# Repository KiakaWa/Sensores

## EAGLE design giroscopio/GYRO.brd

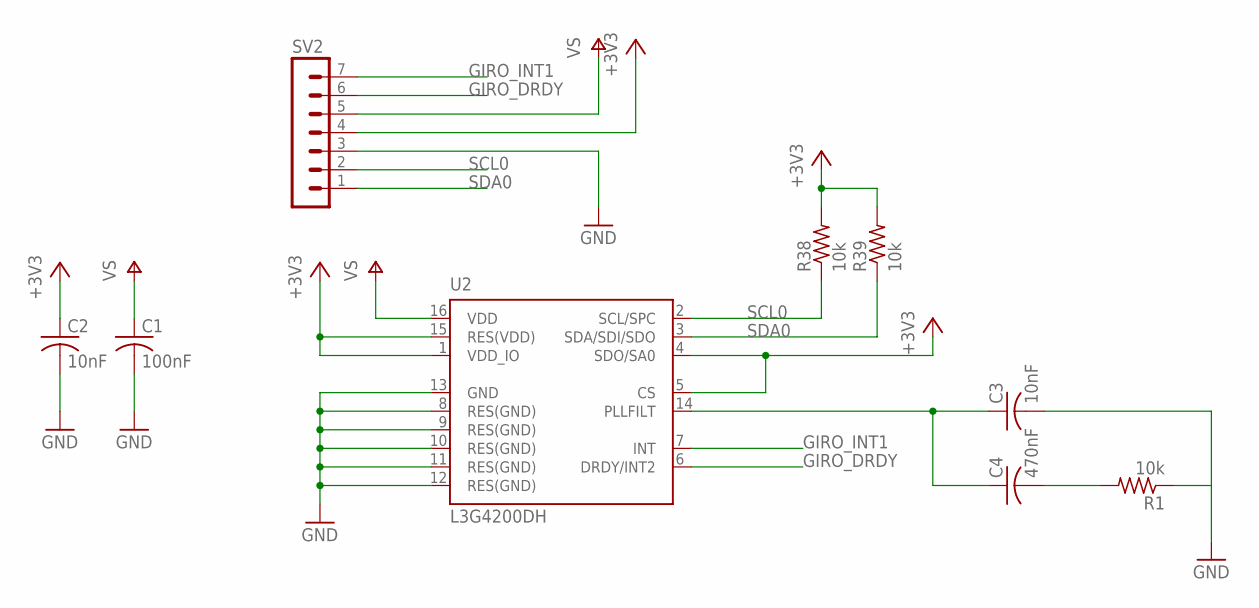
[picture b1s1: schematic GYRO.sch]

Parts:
C1: 100nF; C0805
C2, C3: 10nF; C0805
C4: 470nF; C0805
R1, R38, R39: 10k; R0805
SV2: MA07-1
U2: L3G4200DH; LGA-16L

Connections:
+3V3: C2.1, R38.2, R39.2, SV2.4, U2.1 (VDD_IO), U2.4 (SDO/SA0), U2.5 (CS), U2.15 (RES(VDD))
GIRO_DRDY: SV2.6, U2.6 (DRDY/INT2)
GIRO_INT1: SV2.7, U2.7 (INT)
GND: C1.2, C2.2, C3.2, R1.1, SV2.3, U2.8 (RES(GND)), U2.9 (RES(GND)), U2.10 (RES(GND)), U2.11 (RES(GND)), U2.12 (RES(GND)), U2.13 (GND)
unnamed: C3.1, C4.1, U2.14 (PLLFILT)
unnamed: C4.2, R1.2
SCL0: R38.1, SV2.2, U2.2 (SCL/SPC)
SDA0: R39.1, SV2.1, U2.3 (SDA/SDI/SDO)
V+: C1.1, SV2.5, U2.16 (VDD)

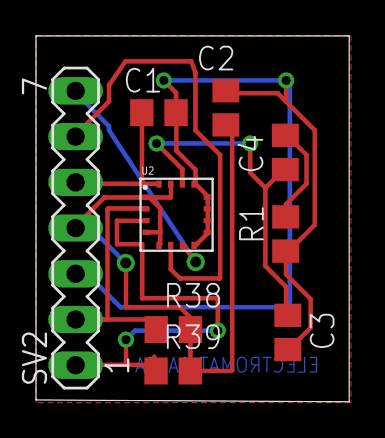
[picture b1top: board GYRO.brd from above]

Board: 2 copper layers, 17.4 x 20.3 mm, 9 parts (0 on the bottom side), 9 nets.

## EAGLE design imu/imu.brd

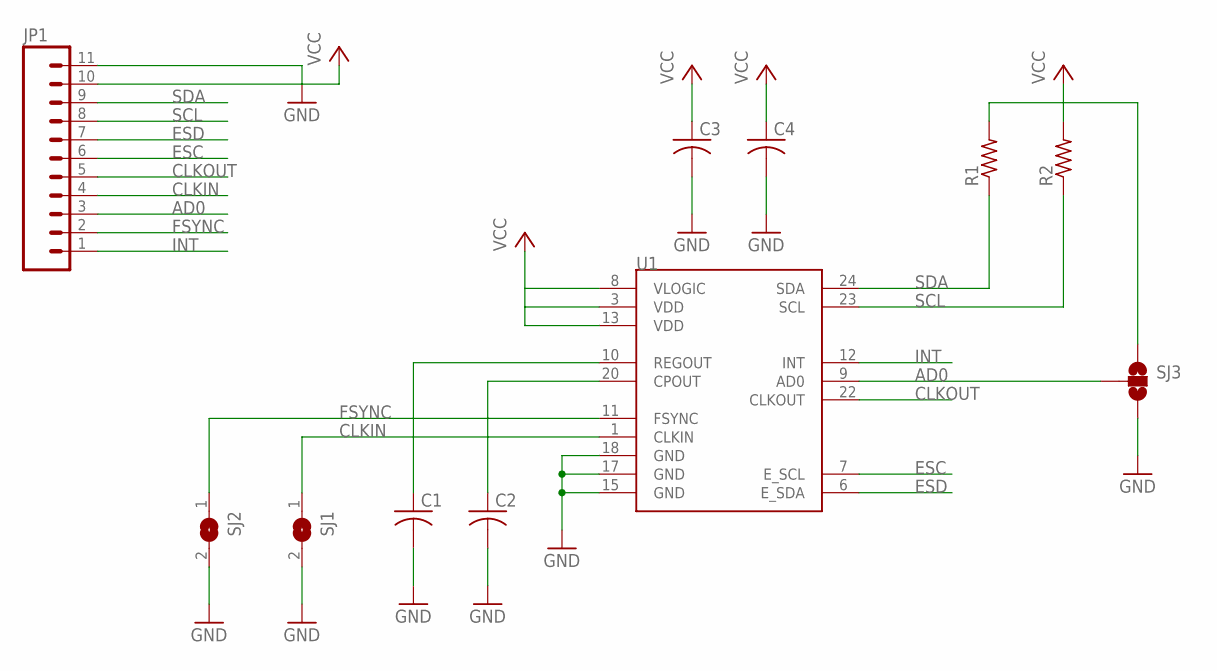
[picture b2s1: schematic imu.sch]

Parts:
C1, C2, C3, C4: C-USC0805; C0805
JP1: M11PTH; 1X11
R1, R2: R-US_R0805; R0805
SJ1, SJ2: SJ
SJ3: SOLDERJUMPER_2WAY-OLDW; SJ_2W
U1: MPU-9150QFN-24-NP; QFN-24-NP

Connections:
AD0: JP1.3, SJ3.2, U1.9 (AD0)
CLKIN: JP1.4, SJ1.1, U1.1 (CLKIN)
CLKOUT: JP1.5, U1.22 (CLKOUT)
ESC: JP1.6, U1.7 (E_SCL)
ESD: JP1.7, U1.6 (E_SDA)
FSYNC: JP1.2, SJ2.1, U1.11 (FSYNC)
GND: C1.2, C2.2, C3.2, C4.2, JP1.11, SJ1.2, SJ2.2, SJ3.3, U1.15 (GND), U1.17 (GND), U1.18 (GND)
INT: JP1.1, U1.12 (INT)
unnamed: C1.1, U1.10 (REGOUT)
unnamed: C2.1, U1.20 (CPOUT)
SCL: JP1.8, R2.1, U1.23 (SCL)
SDA: JP1.9, R1.1, U1.24 (SDA)
VCC: C3.1, C4.1, JP1.10, R1.2, R2.2, SJ3.1, U1.3 (VDD), U1.8 (VLOGIC), U1.13 (VDD)

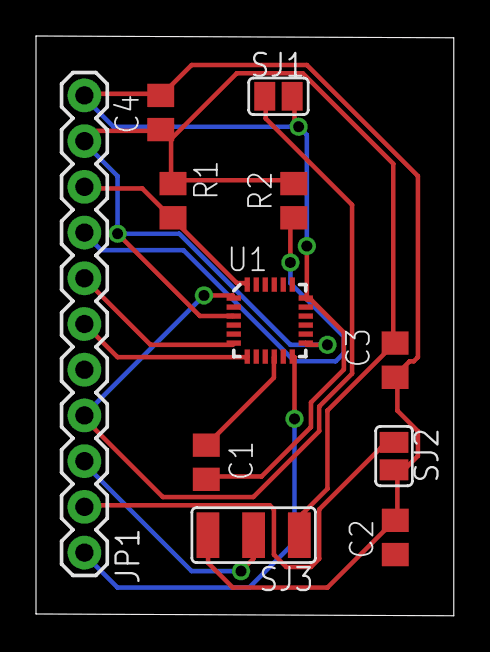
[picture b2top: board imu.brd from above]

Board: 2 copper layers, 23.2 x 32.2 mm, 11 parts (0 on the bottom side), 13 nets.

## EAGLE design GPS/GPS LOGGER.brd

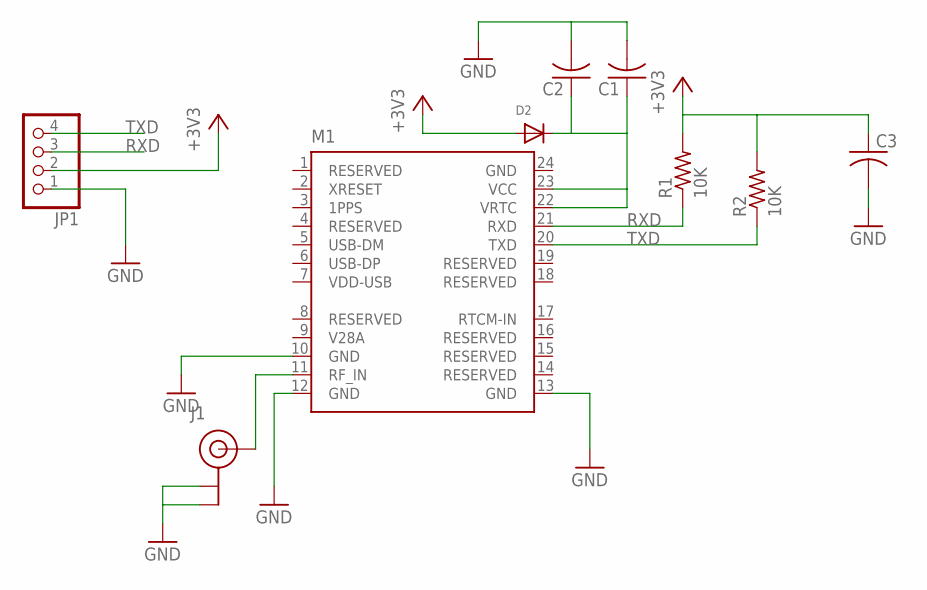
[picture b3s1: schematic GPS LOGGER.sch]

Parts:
C1, C2, C3: C-USC0805; C0805
D2: DIODESOD-323; SOD-323
J1: U.FL
JP1: PINHD-1X4; 1X04
M1: C1216_CONDOR-SMD; 1216
R1, R2: 10K; R0805

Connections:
+3V3: C3.1, D2.A, JP1.2, R1.2, R2.2
GND: C1.2, C2.2, C3.2, J1.P$1 (GND), J1.P$2 (GND), JP1.1, M1.10 (GND), M1.12 (GND), M1.13 (GND), M1.24 (GND)
unnamed: J1.P$3 (SIGNAL), M1.11 (RF_IN)
unnamed: C1.1, C2.1, D2.C, M1.22 (VRTC), M1.23 (VCC)
RXD: JP1.3, M1.21 (RXD), R1.1
TXD: JP1.4, M1.20 (TXD), R2.1

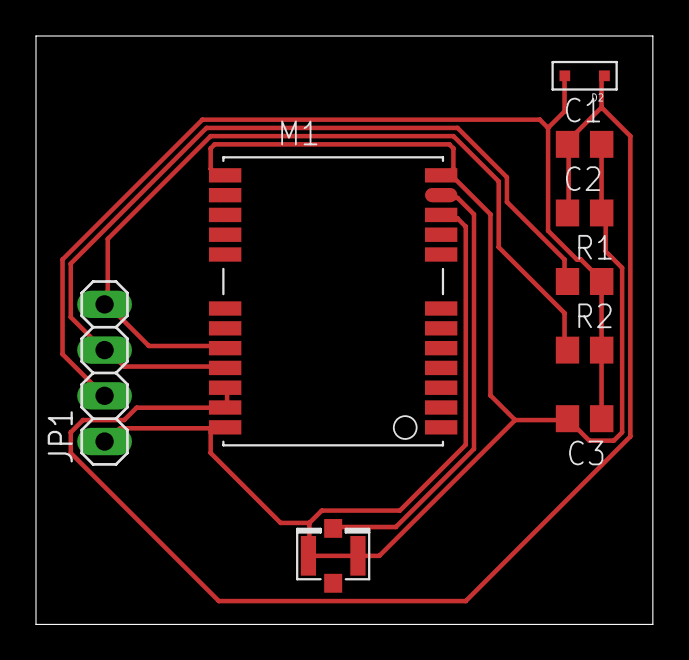
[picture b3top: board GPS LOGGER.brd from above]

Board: 2 copper layers, 34.3 x 32.7 mm, 9 parts (0 on the bottom side), 6 nets.

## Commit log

2016-06-03 Sensores de la placa Electronica
    Completar

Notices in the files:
parts and their libraries:
SparkFun-Connectors: Licensing: Creative Commons ShareAlike 4.0 International - https://creativecommons.org/licenses/by-sa/4.0
